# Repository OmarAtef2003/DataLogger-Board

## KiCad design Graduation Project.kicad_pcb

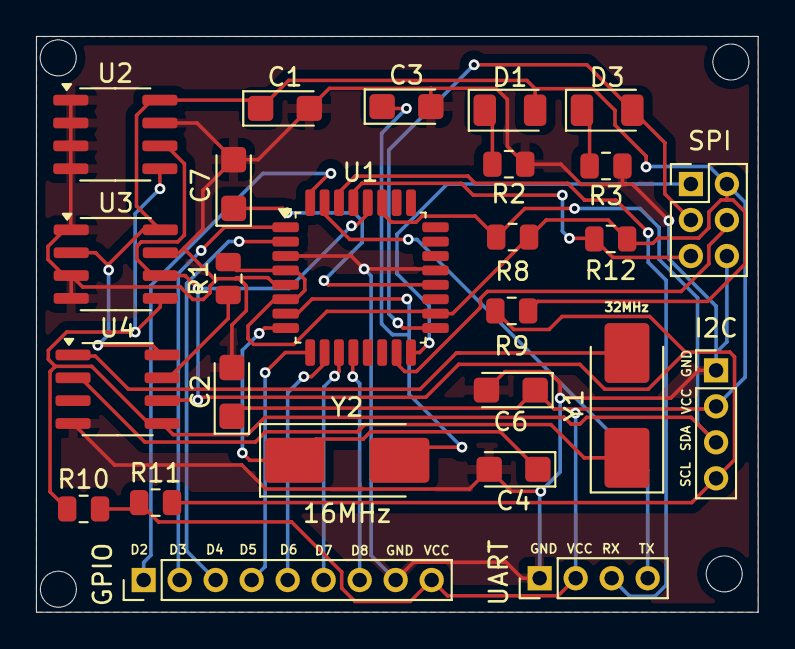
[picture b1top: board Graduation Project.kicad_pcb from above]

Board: 2 copper layers, 40.1 x 32.0 mm, 26 parts (0 on the bottom side), 25 nets.

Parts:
C1, C2, C6, C7: 0.1uF; CP_EIA-3216-18_Kemet-A
C3, C4: 22pF; CP_EIA-3216-18_Kemet-A
D1, D3: LED; LED_1206_3216Metric
GPIO: Conn_01x09_Pin; PinHeader_1x09_P2.00mm_Vertical
I2C: Conn_01x04_Pin; PinHeader_1x04_P2.00mm_Vertical
R1, R12: 10k; R_0805_2012Metric
R2, R3: 330; R_0805_2012Metric
R8, R9, R10, R11: 4.7k; R_0805_2012Metric
SPI: Conn_02x03_Odd_Even; PinHeader_2x03_P2.00mm_Vertical
U1: ATMEGA328P-AUR; TQFP-32_7x7mm_P0.8mm
U2, U3: 24LC1025; SOIC-8_3.9x4.9mm_P1.27mm
U4: DS1337S_; SOIC-8_3.9x4.9mm_P1.27mm
UART: Conn_01x04_Pin; PinHeader_1x04_P2.00mm_Vertical
Y1: 33kHz; Crystal_SMD_0603-2Pin_6.0x3.5mm_HandSoldering
Y2: 16MHz; Crystal_SMD_0603-2Pin_6.0x3.5mm_HandSoldering

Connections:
GND: C1.2, C2.2, C3.2, C4.2, C6.2, C7.2, GPIO.8, I2C.1, R2.1, R3.1, SPI.6, U1.3 (GND), U1.5 (GND), U1.21 (GND), U2.1 (A0), U2.2 (A1), U2.3 (A2), U2.4 (GND), U2.7 (WP), U3.1 (A0), U3.3 (A2), U3.4 (GND), U3.7 (WP), U4.4 (GND), UART.1
MISO: SPI.1, U1.16 (PB4)
MOSI: SPI.4, U1.15 (PB3)
unnamed: D1.1 (K), R2.2
unnamed: D3.1 (K), R3.2
unnamed: C7.1, U1.20 (AREF)
unnamed: C3.1, U1.7 (PB6), Y2.2
unnamed: C4.1, U1.8 (PB7), Y2.1
unnamed: R1.1, U4.7 (SQW/~INT)
unnamed: U4.1 (X1), Y1.2
unnamed: U4.2 (X2), Y1.1
PD2: GPIO.1, U1.32 (PD2)
PD3: GPIO.2, U1.1 (PD3)
PD4: GPIO.3, U1.2 (PD4)
PD5: GPIO.4, U1.9 (PD5)
PD6: GPIO.5, U1.10 (PD6)
PD7: GPIO.6, U1.11 (PD7)
PD8: GPIO.7, U1.12 (PB0)
RESET: R12.1, SPI.5, U1.29 (PC6)
RX: U1.30 (PD0), UART.3
SCK: D3.2 (A), SPI.3, U1.17 (PB5)
SCL: I2C.4, R9.2, R11.2, U1.28 (PC5), U2.6 (SCL), U3.6 (SCL), U4.6 (SCL)
SDA: I2C.3, R8.1, R10.1, U1.27 (PC4), U2.5 (SDA), U3.5 (SDA), U4.5 (SDA)
TX: U1.31 (PD1), UART.4
VCC: C1.1, C2.1, C6.1, D1.2 (A), GPIO.9, I2C.2, R1.2, R8.2, R9.1, R10.2, R11.1, R12.2, SPI.2, U1.4 (VCC), U1.6 (VCC), U1.18 (AVCC), U2.8 (VCC), U3.2 (A1), U3.8 (VCC), U4.8 (VCC), UART.2

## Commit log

2026-05-28 Initial upload – DataLogger Board
2026-05-28 Remove MCU-Datalogger-PCB-Board-Graduation-Project
2026-05-28 Add gitignore
2026-05-28 Remove Graduation Project PDF
